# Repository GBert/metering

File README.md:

Hinweise
========

Tasmota
-------
30 Sekunden Intervall Messwerte ausgeben
500ms Debounce Timer
```
TelePeriod 30
CounterDebounce 80
```

MACOS CH34x Treiber installieren
--------------------------------
https://github.com/adrianmihalko/ch340g-ch34g-ch34x-mac-os-x-driver

Download sonoff-DE.bin von https://github.com/arendst/Sonoff-Tasmota/releases

```
brew install esptool # falls nötig
esptool.py --port /dev/tty.wchusbserial1420 erase_flash
esptool.py --port /dev/tty.wchusbserial1420 write_flash --flash_size=detect 0 sonoff-DE.bin
```

Amazon Dash -> tcpdump erlauben

```
sudo setcap 'CAP_NET_RAW+eip CAP_NET_ADMIN+eip' /usr/bin/node
```

Debounce Code anpassen ?
------------------------
https://hackaday.com/2010/11/09/debounce-code-one-post-to-rule-them-all/

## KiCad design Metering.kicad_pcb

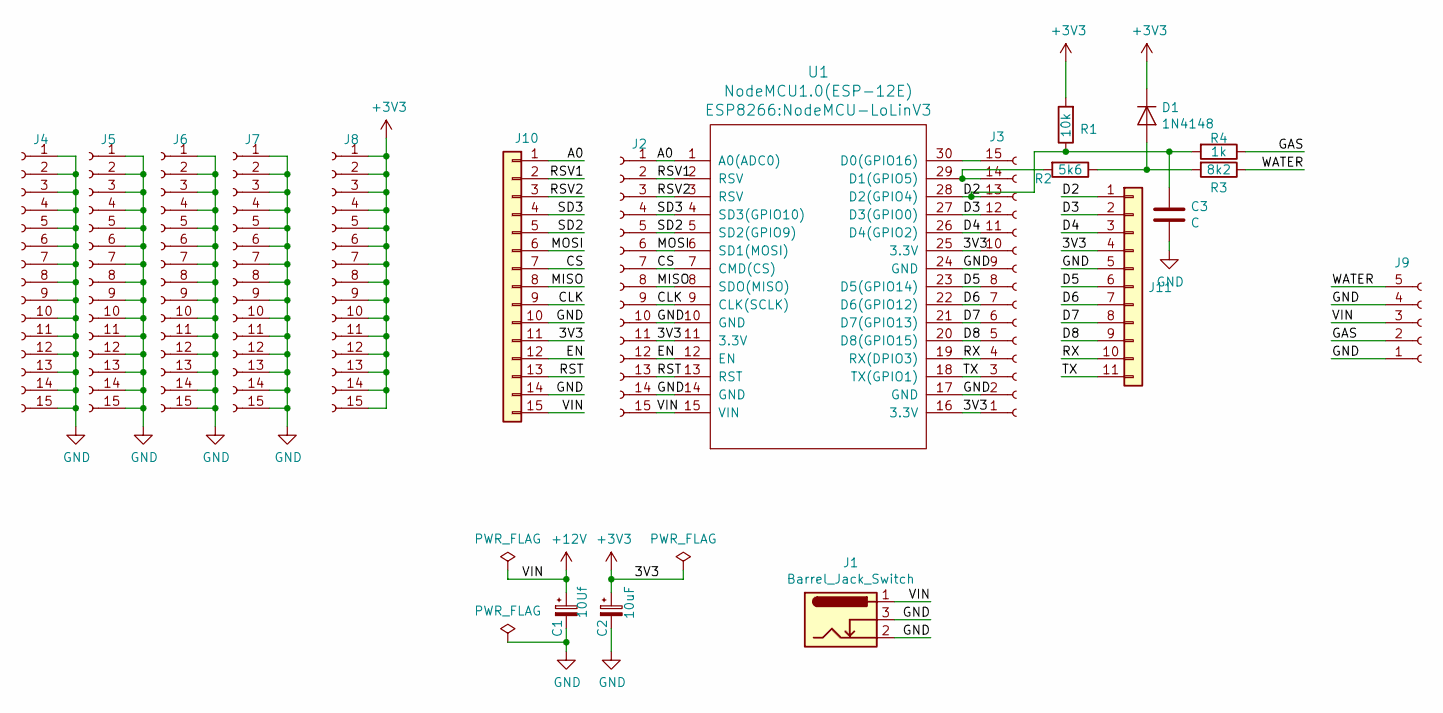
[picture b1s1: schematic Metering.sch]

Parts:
C1: 10Uf; CP_5x7mm
C2: 10uF; CP_5x7mm
C3: C; C_Disc_D3.0mm_W2.0mm_P2.50mm
D1: 1N4148; D_DO-35_SOD27_P7.62mm_Horizontal
J1: Barrel_Jack_Switch; dc_socket
J2, J3, J4, J5, J6, J7, J8: Conn_01x15_Female; PinHeader_1x15_P2.54mm_Vertical
J9: Conn_01x05_Female; mkds_1,5-5
J10: Conn_01x15; PinHeader_1x15_P2.54mm_Vertical
J11: Conn_01x11; PinHeader_1x11_P2.54mm_Vertical
R1: 10k; RC03
R2: 5k6; RC03
R3: 8k2; RC03
R4: 1k; RC03
U1: NodeMCU1.0(ESP-12E); NodeMCU-LoLinV3

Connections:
+3V3: C2.1, D1.1 (K), J2.11, J3.1, J3.10, J8.1, J8.2, J8.3, J8.4, J8.5, J8.6, J8.7, J8.8, J8.9, J8.10, J8.11, J8.12, J8.13, J8.14, J8.15, J10.11, J11.4, R1.2, U1.11 (3.3V), U1.16 (3.3V), U1.25 (3.3V)
+12V: C1.1, J1.1, J2.15, J9.3, J10.15, U1.15 (VIN)
/A0: J2.1, J10.1, U1.1 (A0(ADC0))
/CLK: J2.9, J10.9, U1.9 (CLK(SCLK))
/CS: J2.7, J10.7, U1.7 (CMD(CS))
/D2: C3.1, J3.13, J11.1, R1.1, R4.2, U1.28 (D2(GPIO4))
/D3: J3.12, J11.2, U1.27 (D3(GPIO0))
/D4: J3.11, J11.3, U1.26 (D4(GPIO2))
/D5: J3.8, J11.6, U1.23 (D5(GPIO14))
/D6: J3.7, J11.7, U1.22 (D6(GPIO12))
/D7: J3.6, J11.8, U1.21 (D7(GPIO13))
/D8: J3.5, J11.9, U1.20 (D8(GPIO15))
/EN: J2.12, J10.12, U1.12 (EN)
/GAS: J9.2, R4.1
/MISO: J2.8, J10.8, U1.8 (SDO(MISO))
/MOSI: J2.6, J10.6, U1.6 (SD1(MOSI))
/RST: J2.13, J10.13, U1.13 (RST)
/RSV1: J2.2, J10.2, U1.2 (RSV)
/RSV2: J2.3, J10.3, U1.3 (RSV)
/RX: J3.4, J11.10, U1.19 (RX(DPIO3))
/SD2: J2.5, J10.5, U1.5 (SD2(GPIO9))
/SD3: J2.4, J10.4, U1.4 (SD3(GPIO10))
/TX: J3.3, J11.11, U1.18 (TX(GPIO1))
/WATER: J9.5, R3.1
GND: C1.2, C2.2, C3.2, J1.2, J1.3, J2.10, J2.14, J3.2, J3.9, J4.1, J4.2, J4.3, J4.4, J4.5, J4.6, J4.7, J4.8, J4.9, J4.10, J4.11, J4.12, J4.13, J4.14, J4.15, J5.1, J5.2, J5.3, J5.4, J5.5, J5.6, J5.7, J5.8, J5.9, J5.10, J5.11, J5.12, J5.13, J5.14, J5.15, J6.1, J6.2, J6.3, J6.4, J6.5, J6.6, J6.7, J6.8, J6.9, J6.10, J6.11, J6.12, J6.13, J6.14, J6.15, J7.1, J7.2, J7.3, J7.4, J7.5, J7.6, J7.7, J7.8, J7.9, J7.10, J7.11, J7.12, J7.13, J7.14, J7.15, J9.1, J9.4, J10.10, J10.14, J11.5, U1.10 (GND), U1.14 (GND), U1.17 (GND), U1.24 (GND)
unnamed: D1.2 (A), R2.1, R3.2
unnamed: J3.14, R2.2, U1.29 (D1(GPIO5))
unnamed: J3.15, U1.30 (D0(GPIO16))

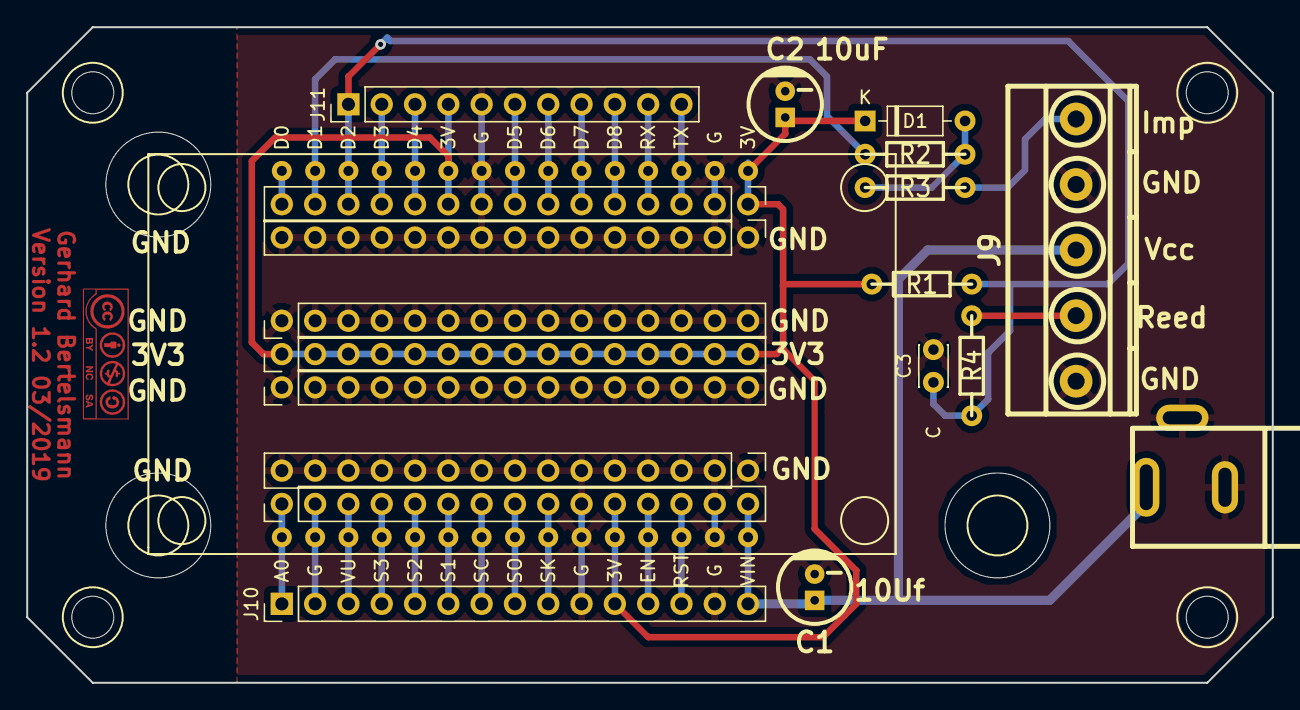
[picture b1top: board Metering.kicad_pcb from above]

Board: 2 copper layers, 95.0 x 50.0 mm, 20 parts (0 on the bottom side), 28 nets.

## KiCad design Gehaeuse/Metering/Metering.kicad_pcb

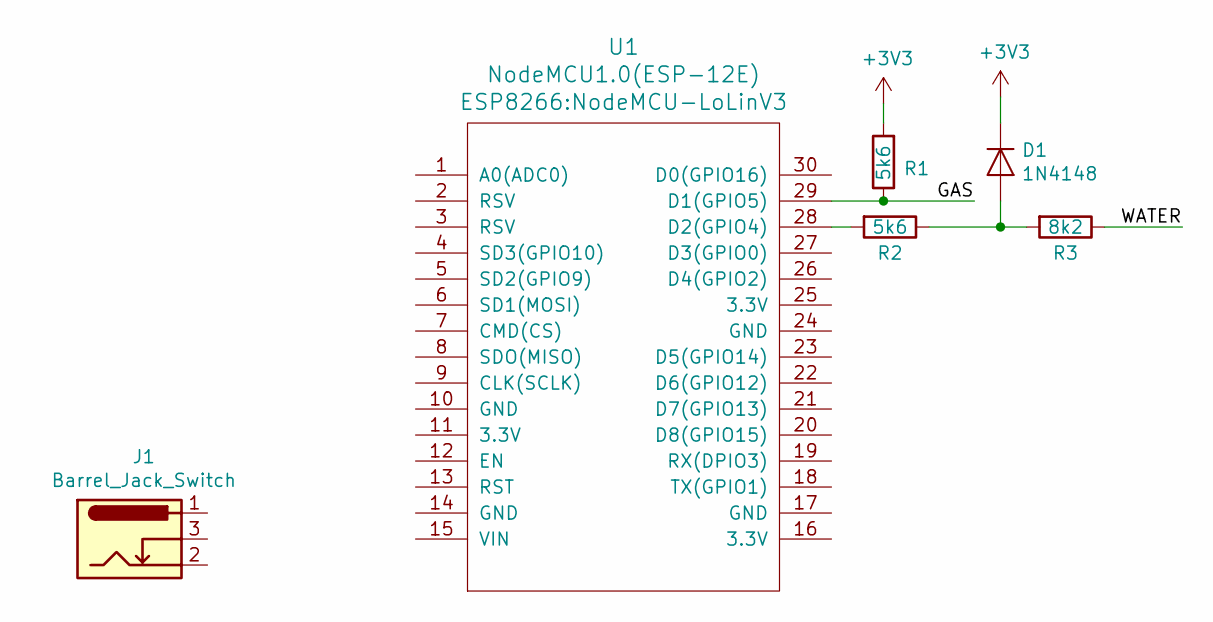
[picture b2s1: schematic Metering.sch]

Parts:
D1: 1N4148; D_DO-35_SOD27_P7.62mm_Horizontal
J1: Barrel_Jack_Switch; dc_socket
R1, R2: 5k6; RC03
R3: 8k2; RC03
U1: NodeMCU1.0(ESP-12E); NodeMCU-LoLinV3

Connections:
+3V3: D1.1 (K), R1.2
/GAS: R1.1, U1.29 (D1(GPIO5))
/WATER: R3.1
unnamed: D1.2 (A), R2.1, R3.2
unnamed: R2.2, U1.28 (D2(GPIO4))

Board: 2 copper layers, 6 parts (0 on the bottom side), 4 nets, no tracks yet.

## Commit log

2019-01-21 starting ...
2019-01-21 version 1.0
2019-02-08 add drills
2019-02-28 move document
2019-03-04 add script for RRD
2019-03-04 add IR housing
2019-03-05 use more polygons
2019-03-05 my first self designed housing
2019-03-06 shorten board and use D2 instead of D0
2019-03-09 add SML test data
2019-03-11 enlarged the hole
2019-03-11 save gas counter sensor clip
2019-03-11 adding hole
2019-03-12 house keeping
2019-03-13 add TCRT mod pic
2019-03-13 show debouncing with original and modified module
2019-03-14 add TCRT5000 modding schematic
2019-05-12 add PDF schematic
